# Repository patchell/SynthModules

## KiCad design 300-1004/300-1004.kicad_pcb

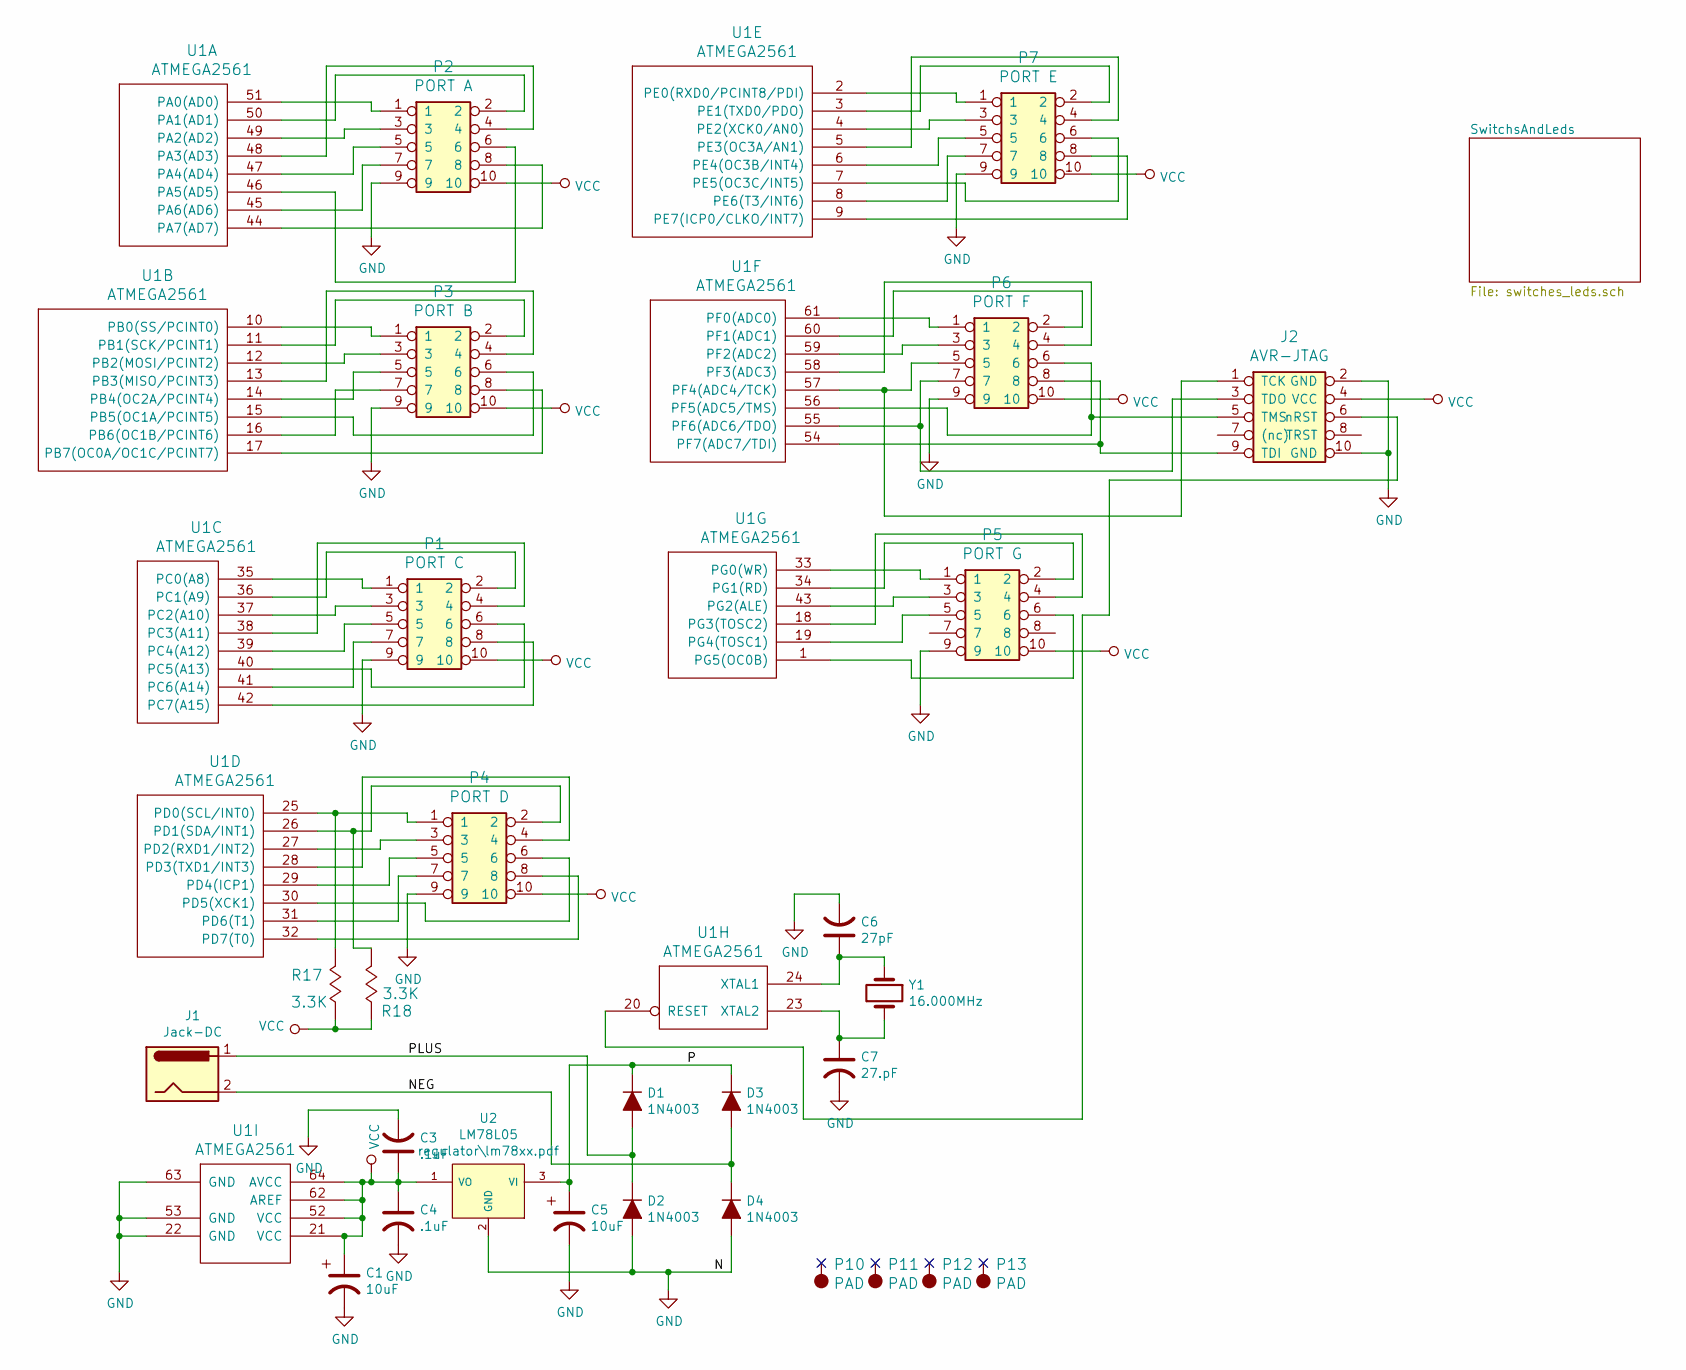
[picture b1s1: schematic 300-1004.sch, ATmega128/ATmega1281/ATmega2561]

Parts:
C1: 10uF; Cap-Pol-Rad-0.2_0.1
C3, C4: .1uF; C_0603_HandSoldering
C5: 10uF; CapPol-Rad-0.2x0.1
C6: 27pF; C_0603_HandSoldering
C7: 27.pF; C_0603_HandSoldering
D1, D2, D3, D4: 1N4003; DIODE0.4
J1: Jack-DC; DC-JACK-CUI-PJ-085AH
J2: AVR-JTAG; IDC5x2_Vert
P1: PORT C; IDC5x2_Vert
P2: PORT A; IDC5x2_Vert
P3: PORT B; IDC5x2_Vert
P4: PORT D; IDC5x2_Vert
P5: PORT G; IDC5x2_Vert
P6: PORT F; IDC5x2_Vert
P7: PORT E; IDC5x2_Vert
P10, P11, P12, P13: PAD
R17, R18: 3.3K; AXIAL0_4
U1: ATMEGA2561; TQFP-64_14x14mm_Pitch0.8mm
U2: LM78L05; TO92
Y1: 16.000MHz; XTAL

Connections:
/NEG: D3.2 (A), D4.1 (K), J1.2
/P: C5.1, D1.1 (K), D3.1 (K), U2.3 (VI)
/PLUS: D1.2 (A), D2.1 (K), J1.1
GND: C1.2, C3.2, C4.2, C5.2, C6.2, C7.2, D2.2 (A), D4.2 (A), J2.2 (GND), J2.10 (GND), P1.9, P2.9, P3.9, P4.9, P5.9, P6.9, P7.9, U1.22 (GND), U1.53 (GND), U1.63 (GND), U2.2 (GND); also elsewhere on the board
unnamed: C6.1, U1.24 (XTAL1), Y1.1
unnamed: C7.1, U1.23 (XTAL2), Y1.2
unnamed: J2.1 (TCK), P6.5, U1.57 (PF4(ADC4/TCK))
unnamed: J2.3 (TDO), P6.7, U1.55 (PF6(ADC6/TDO))
unnamed: J2.5 (TMS), P6.6, U1.56 (PF5(ADC5/TMS))
unnamed: J2.6 (nRST), U1.20 (RESET)
unnamed: J2.9 (TDI), P6.8, U1.54 (PF7(ADC7/TDI))
unnamed: P1.1, U1.35 (PC0(A8))
unnamed: P1.2, U1.36 (PC1(A9))
unnamed: P1.3, U1.37 (PC2(A10))
unnamed: P1.4, U1.38 (PC3(A11))
unnamed: P1.5, U1.39 (PC4(A12))
unnamed: P1.6, U1.40 (PC5(A13))
unnamed: P1.7, U1.41 (PC6(A14))
unnamed: P1.8, U1.42 (PC7(A15))
unnamed: P2.1, U1.51 (PA0(AD0))
unnamed: P2.2, U1.50 (PA1(AD1))
unnamed: P2.3, U1.49 (PA2(AD2))
unnamed: P2.4, U1.48 (PA3(AD3))
unnamed: P2.5, U1.47 (PA4(AD4))
unnamed: P2.6, U1.46 (PA5(AD5))
unnamed: P2.7, U1.45 (PA6(AD6))
unnamed: P2.8, U1.44 (PA7(AD7))
unnamed: P3.1, U1.10 (PB0(SS/PCINT0))
unnamed: P3.2, U1.11 (PB1(SCK/PCINT1))
unnamed: P3.3, U1.12 (PB2(MOSI/PCINT2))
unnamed: P3.4, U1.13 (PB3(MISO/PCINT3))
unnamed: P3.5, U1.14 (PB4(OC2A/PCINT4))
unnamed: P3.6, U1.15 (PB5(OC1A/PCINT5))
unnamed: P3.7, U1.16 (PB6(OC1B/PCINT6))
unnamed: P3.8, U1.17 (PB7(OC0A/OC1C/PCINT7))
unnamed: P4.1, R17.2 (B), U1.25 (PD0(SCL/INT0))
unnamed: P4.2, R18.2 (B), U1.26 (PD1(SDA/INT1))
unnamed: P4.3, U1.27 (PD2(RXD1/INT2))
unnamed: P4.4, U1.28 (PD3(TXD1/INT3))
unnamed: P4.5, U1.29 (PD4(ICP1))
unnamed: P4.6, U1.30 (PD5(XCK1))
unnamed: P4.7, U1.31 (PD6(T1))
unnamed: P4.8, U1.32 (PD7(T0))
unnamed: P5.1, U1.33 (PG0(WR))
unnamed: P5.2, U1.34 (PG1(RD))
unnamed: P5.3, U1.43 (PG2(ALE))
unnamed: P5.4, U1.18 (PG3(TOSC2))
unnamed: P5.5, U1.19 (PG4(TOSC1))
unnamed: P5.6, U1.1 (PG5(OC0B))
unnamed: P6.1, U1.61 (PF0(ADC0))
unnamed: P6.2, U1.60 (PF1(ADC1))
unnamed: P6.3, U1.59 (PF2(ADC2))
unnamed: P6.4, U1.58 (PF3(ADC3))
unnamed: P7.1, U1.2 (PE0(RXD0/PCINT8/PDI))
unnamed: P7.2, U1.3 (PE1(TXD0/PDO))
unnamed: P7.3, U1.4 (PE2(XCK0/AN0))
unnamed: P7.4, U1.5 (PE3(OC3A/AN1))
unnamed: P7.5, U1.6 (PE4(OC3B/INT4))
unnamed: P7.6, U1.7 (PE5(OC3C/INT5))
unnamed: P7.7, U1.8 (PE6(T3/INT6))
unnamed: P7.8, U1.9 (PE7(ICP0/CLKO/INT7))
VCC: C1.1, C3.1, C4.1, J2.4 (VCC), P1.10, P2.10, P3.10, P4.10, P5.10, P6.10, P7.10, R17.1 (A), R18.1 (A), U1.21 (VCC), U1.52 (VCC), U1.62 (AREF), U1.64 (AVCC), U2.1 (VO); also elsewhere on the board

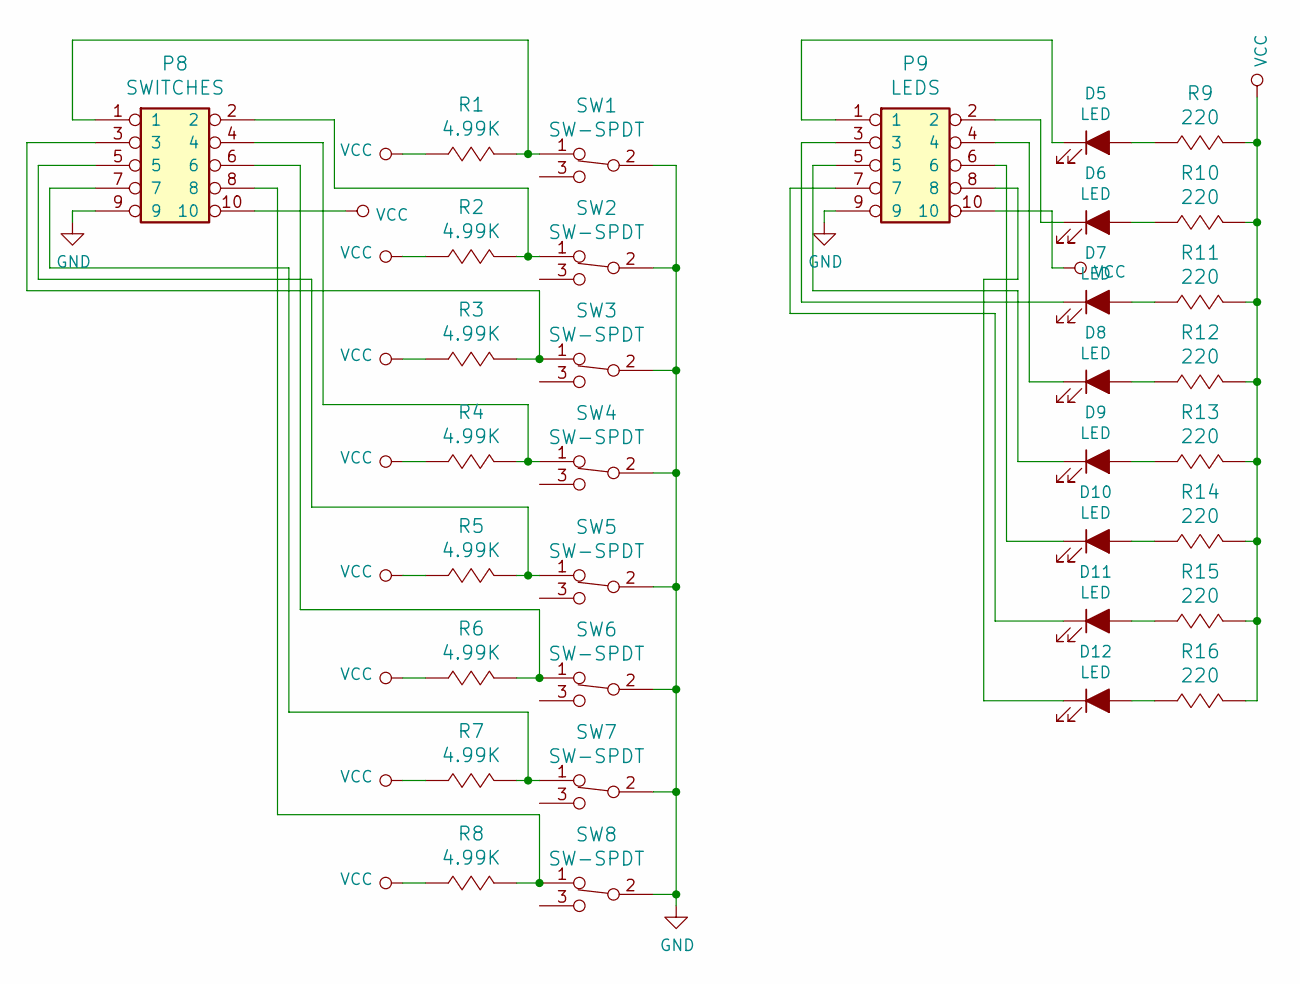
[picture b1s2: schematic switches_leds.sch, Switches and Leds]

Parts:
D5, D6, D7, D8, D9, D10, D11, D12: LED; LED_5.0mm
P8: SWITCHES; IDC5x2_Vert
P9: LEDS; IDC5x2_Vert
R1, R2, R3, R4, R5, R6, R7, R8: 4.99K; AXIAL0_4
R9, R10, R11, R12, R13, R14, R15, R16: 220; AXIAL0_4
SW1, SW2, SW3, SW4, SW5, SW6, SW7, SW8: SW-SPDT; SWITCH_SPDT-OS102011MS2QN1; Part# 611-OS102011MS2QN1

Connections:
GND: P8.9, P9.9, SW1.2, SW2.2, SW3.2, SW4.2, SW5.2, SW6.2, SW7.2, SW8.2; also elsewhere on the board
unnamed: D5.1 (K), P9.1
unnamed: D5.2 (A), R9.1 (A)
unnamed: D6.1 (K), P9.2
unnamed: D6.2 (A), R10.1 (A)
unnamed: D7.1 (K), P9.3
unnamed: D7.2 (A), R11.1 (A)
unnamed: D8.1 (K), P9.4
unnamed: D8.2 (A), R12.1 (A)
unnamed: D9.1 (K), P9.5
unnamed: D9.2 (A), R13.1 (A)
unnamed: D10.1 (K), P9.6
unnamed: D10.2 (A), R14.1 (A)
unnamed: D11.1 (K), P9.7
unnamed: D11.2 (A), R15.1 (A)
unnamed: D12.1 (K), P9.8
unnamed: D12.2 (A), R16.1 (A)
unnamed: P8.1, R1.2 (B), SW1.1
unnamed: P8.2, R2.2 (B), SW2.1
unnamed: P8.3, R3.2 (B), SW3.1
unnamed: P8.4, R4.2 (B), SW4.1
unnamed: P8.5, R5.2 (B), SW5.1
unnamed: P8.6, R6.2 (B), SW6.1
unnamed: P8.7, R7.2 (B), SW7.1
unnamed: P8.8, R8.2 (B), SW8.1
VCC: P8.10, P9.10, R1.1 (A), R2.1 (A), R3.1 (A), R4.1 (A), R5.1 (A), R6.1 (A), R7.1 (A), R8.1 (A), R9.2 (B), R10.2 (B), R11.2 (B), R12.2 (B), R13.2 (B), R14.2 (B), R15.2 (B), R16.2 (B); also elsewhere on the board

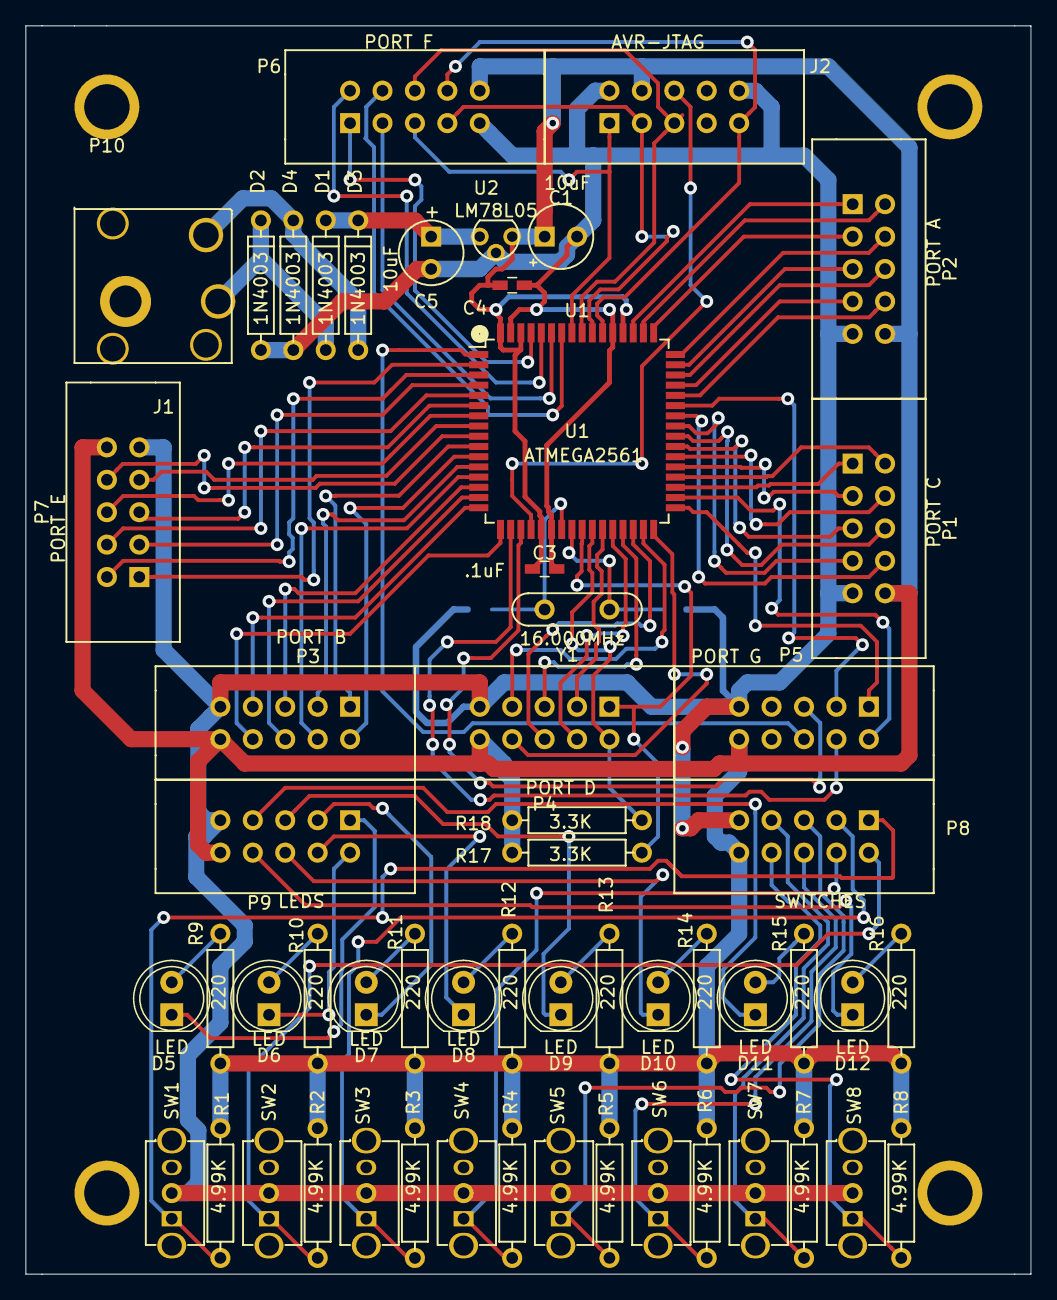
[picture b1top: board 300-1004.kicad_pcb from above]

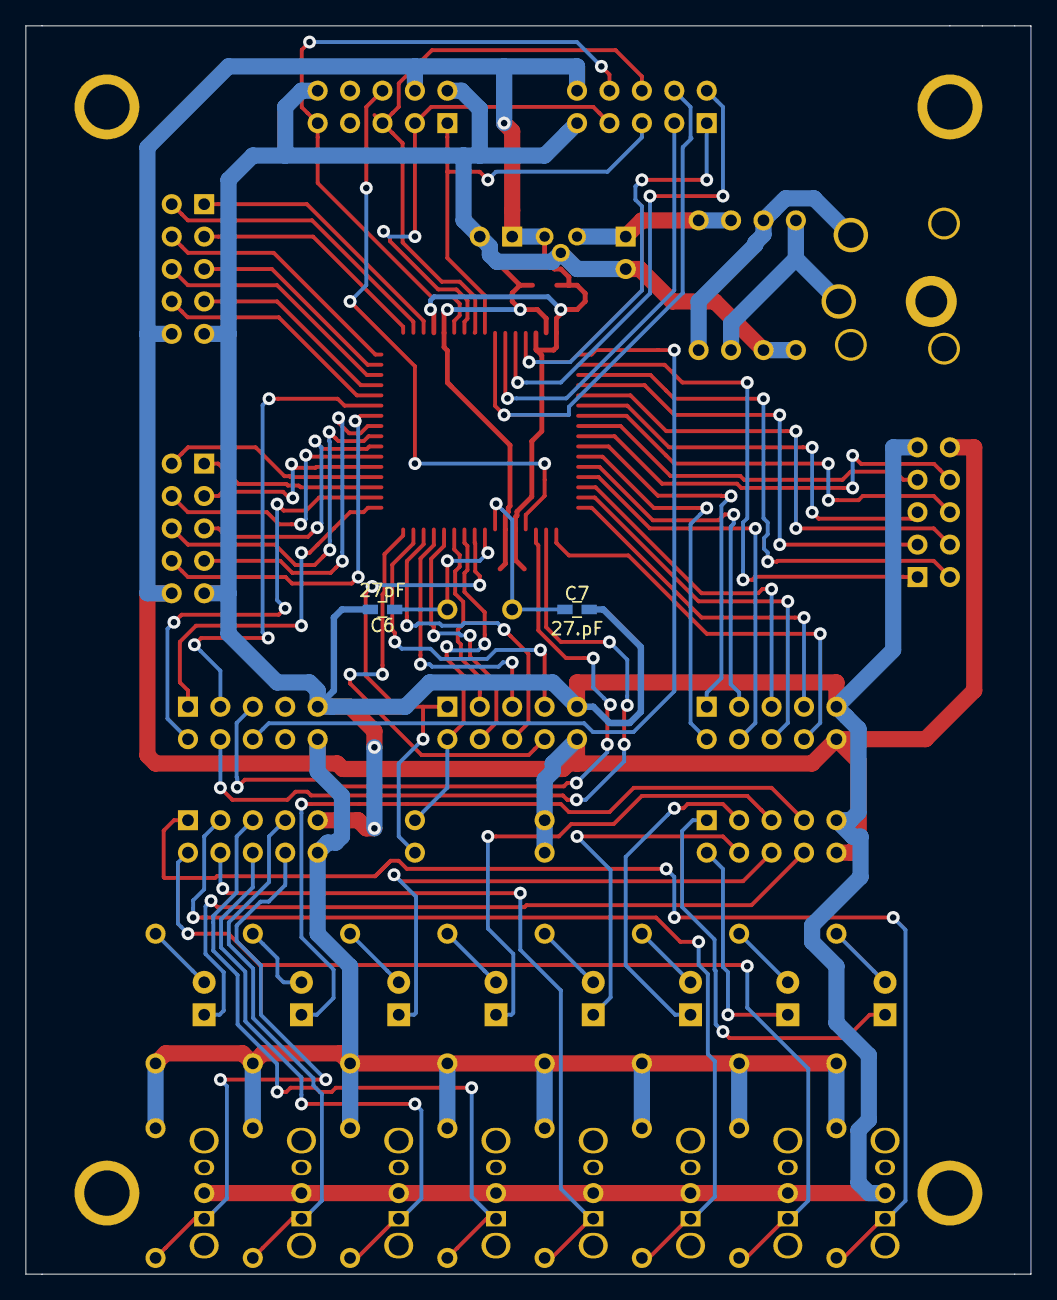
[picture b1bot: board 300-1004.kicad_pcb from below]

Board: 2 copper layers, 78.7 x 97.8 mm, 62 parts (2 on the bottom side), 86 nets.

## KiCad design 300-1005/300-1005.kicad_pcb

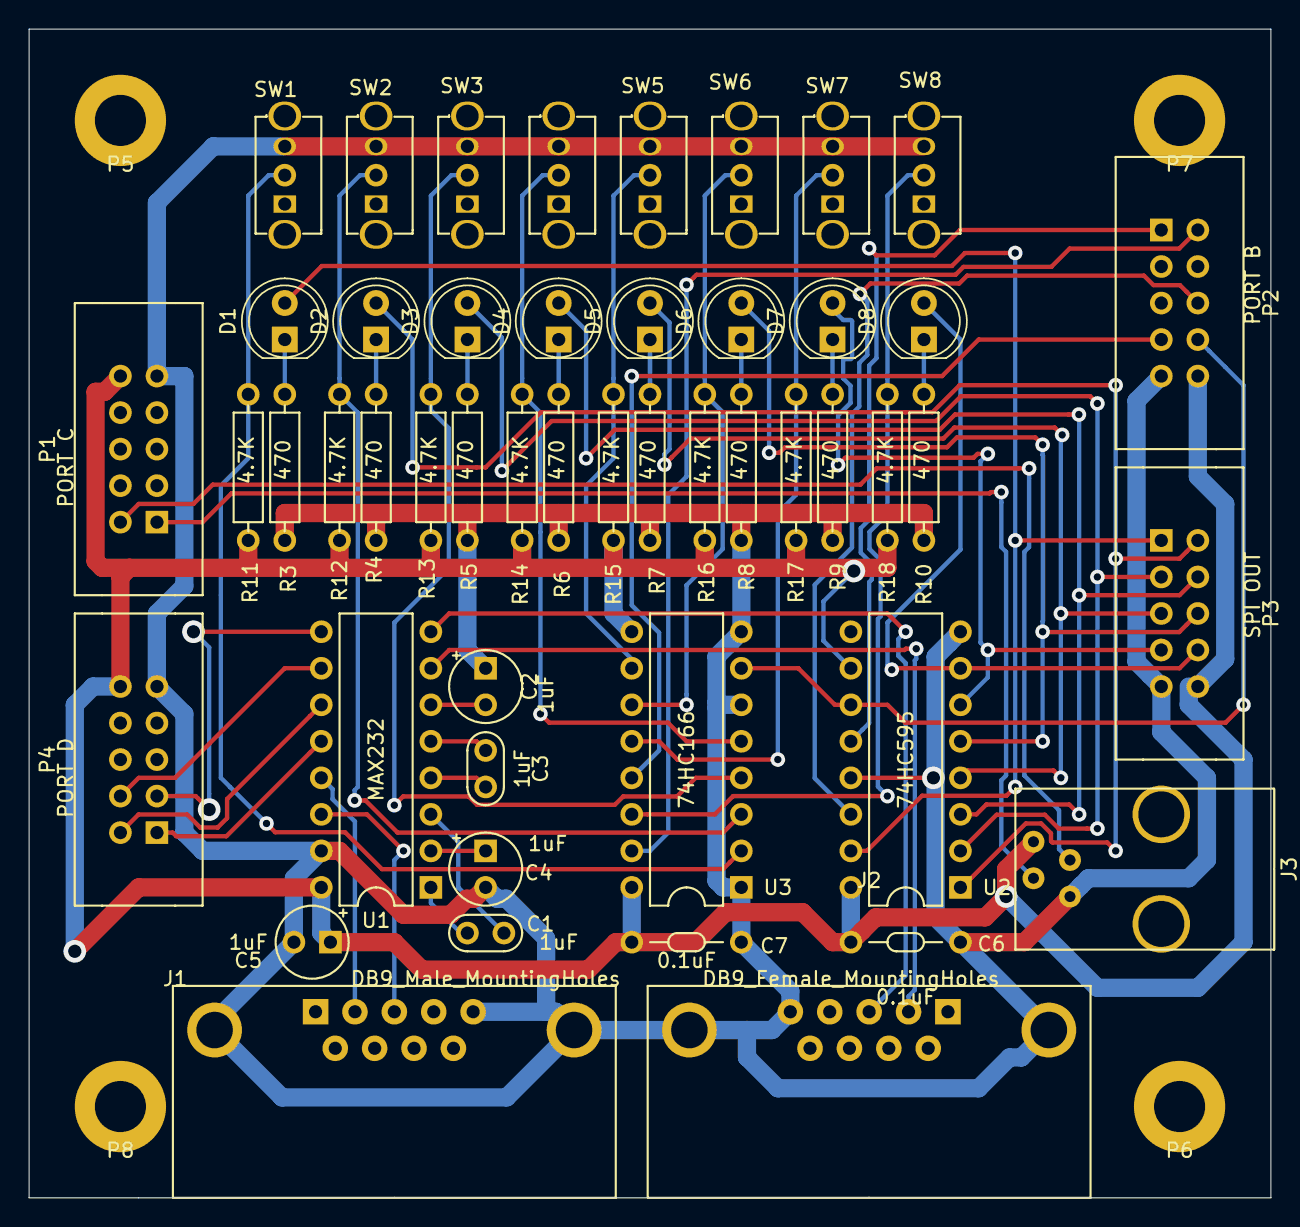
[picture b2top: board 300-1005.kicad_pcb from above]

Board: 2 copper layers, 86.4 x 81.3 mm, 53 parts (0 on the bottom side), 47 nets.

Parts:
C1, C3: 1uF; CAP-0.1
C2, C4, C5: 1uF; Cap-Pol-Rad-0.2_0.1
C6, C7: 0.1uF; CAP-Bypass-0_3
D1, D2, D3, D4, D5, D6, D7, D8: LED; LED_5.0mm
J1: DB9_Male_MountingHoles; DSUB-9P
J2: DB9_Female_MountingHoles; DSUB-9S
J3: RJ9; RJ9-PCB-Conn
P1: PORT C; IDC5x2_Vert
P2: PORT B; IDC5x2_Vert
P3: SPI OUT; IDC5x2_Vert
P4: PORT D; IDC5x2_Vert
P5, P6, P7, P8: PAD
R3, R4, R5, R6, R7, R8, R9, R10: 470; AXIAL0_4
R11, R12, R13, R14, R15, R16, R17, R18: 4.7K; AXIAL0_4
SW1, SW2, SW3, SW4, SW5, SW6, SW7, SW8: SW-SPDT; SWITCH_SPDT-OS102011MS2QN1
U1: MAX232; DIP-16
U2: 74HC595; DIP-16
U3: 74HC166; DIP-16

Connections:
+5V0: C5.1, C6.1, C7.1, J3.4, P1.10, P2.10, P3.10, P4.10, R11.2, R12.2, R13.2, R14.2, R15.2, R16.2, R17.2, R18.2, U1.16, U2.10, U2.16, U3.9, U3.16
/LATCH_SERIN: P2.2, U3.15
/LATCH_SEROUT: P2.1, U2.12
/MISO: P2.7, U3.13
/MOSI: P2.6, U2.14
/RXD0: P4.1, U1.12
/RXD1: P4.3, U1.9
/S1: R11.1, SW1.2, U3.2
/S2: R12.1, SW2.2, U3.3
/S3: R13.1, SW3.2, U3.4
/S4: R14.1, SW4.2, U3.5
/S5: R15.1, SW5.2, U3.10
/S6: R16.1, SW6.2, U3.11
/S7: R17.1, SW7.2, U3.12
/S8: R18.1, SW8.2, U3.14
/SCK: P2.8, U2.11, U3.7
/SCL: J3.2, P1.1
/SDA: J3.3, P1.2
/SPI0: D1.2, P3.1, U2.15
/SPI1: D2.2, P3.2, U2.1
/SPI2: D3.2, P3.3, U2.2
/SPI3: D4.2, P3.4, U2.3
/SPI4: D5.2, P3.5, U2.4
/SPI5: D6.2, P3.6, U2.5
/SPI6: D7.2, P3.7, U2.6
/SPI7: D8.2, P3.8, U2.7
/TXD0: P4.2, U1.11
/TXD1: P4.4, U1.10
GND: C2.1, C4.2, C5.2, C6.2, C7.2, J1.0, J1.5, J2.0, J2.5, J3.1, P1.9, P2.9, P3.9, P4.9, R3.2, R4.2, R5.2, R6.2, R7.2, R8.2, R9.2, R10.2, SW1.3, SW2.3, SW3.3, SW4.3, SW5.3, SW6.3, SW7.3, SW8.3, U1.15, U2.8, U2.13, U3.1, U3.6, U3.8
unnamed: C1.1, U1.1
unnamed: C1.2, U1.3
unnamed: C2.2, U1.6
unnamed: C3.1, U1.4
unnamed: C3.2, U1.5
unnamed: C4.1, U1.2
unnamed: D1.1, R3.1
unnamed: D2.1, R4.1
unnamed: D3.1, R5.1
unnamed: D4.1, R6.1
unnamed: D5.1, R7.1
unnamed: D6.1, R8.1
unnamed: D7.1, R9.1
unnamed: D8.1, R10.1
unnamed: J1.2, U1.13
unnamed: J1.3, U1.14
unnamed: J2.2, U1.7
unnamed: J2.3, U1.8

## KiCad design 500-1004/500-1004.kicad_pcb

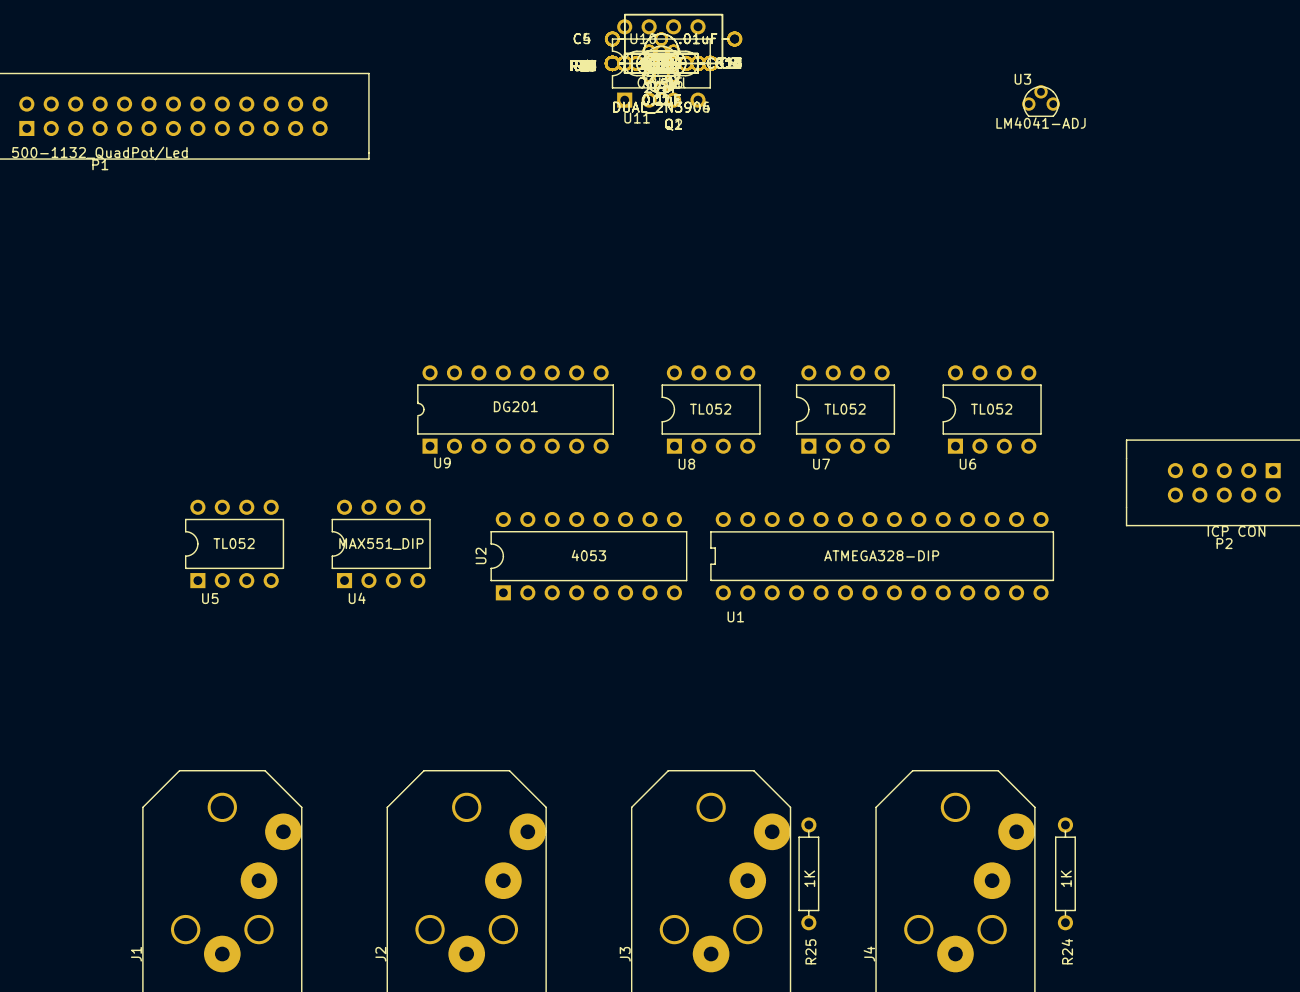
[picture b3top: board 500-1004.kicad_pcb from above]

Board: 2 copper layers, 67 parts (0 on the bottom side), 59 nets, no tracks yet.

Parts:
C1, C2: 27pF; CAP-0.1
C3, C6: Cap; CAP-GREENIE-0.2
C4, C5: .01uF; CAP-AXIAL-0.5x0.2
C7, C8, C9, C10, C11, C12, C13, C14, C15, C16, C17: 0.1uF; CAP-Bypass-0.3
D1, D2, D3, D4, D5: D_ALT; DIODE0.4
J1: GATE; PHONE-SC112A
J2, J3, J4: OUT; PHONE-SC112A
P1: 500-1132_QuadPot/Led; IDC-13x2
P2: ICP CON; IDC5x2_Vert
Q1: DUAL_2N3904; DUAL_TO92
Q2: DUAL_2N3906; DUAL_TO92
R1, R6, R7, R8, R9, R10, R11, R12, R13, R14, R15, R19, R20: 100K; AXIAL0.4
R2, R3, R4, R5: 470; AXIAL0.4
R16, R18, R22: 10K; AXIAL0.4
R17, R21: 182; AXIAL0.4
R23, R24, R25: 1K; AXIAL0.4
U1: ATMEGA328-DIP; DIP28.3
U2: 4053; DIP-16.3
U3: LM4041-ADJ; TO92
U4: MAX551_DIP; DIP8.3
U5, U6, U7, U8, U11: TL052; DIP8.3
U9: DG201; DIP16.3
U10: 78L05; TO92
Y1: Crystal; XTAL

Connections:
+15V0: C7.1, C8.1, C10.1, C11.1, C15.1, R13.1, U5.8, U6.8, U8.8, U9.13, U10.3, U11.8
-15V0: C9.1, C12.1, C13.1, C14.1, C16.1, R8.2, R15.2, U5.4, U6.4, U8.4, U9.4, U11.4
/ATTACK: P1.2, U1.23
/DECAY: P1.6, U1.24
/DONE: D5.1, R20.1, U1.4
/GATE: D1.1, D2.2, R1.1, U1.5
/LD_DAC: U1.2, U4.4
/LED0: R2.2, U1.6
/LED1: R3.2, U1.11
/LED2: R4.2, U1.12
/LED3: R5.2, U1.13
/MISO: U1.18, U2.15
/MOSI: U1.17, U2.14
/RELEASE: P1.14, U1.26
/RST: P2.5, U1.1, U2.9, U2.10, U2.11
/SCK: U1.19, U2.4
/SH0: U1.14, U9.1
/SH1: U1.15, U9.8
/SUSTAIN: P1.10, U1.25
GND: C1.2, C2.2, C4.2, C5.2, C7.2, C8.2, C9.2, C10.2, C11.2, C12.2, C13.2, C14.2, C15.2, C16.2, C17.2, D1.2, D5.2, J1.1, J2.1, J3.1, J4.1, P1.3, P1.7, P1.11, P1.15, P2.4, P2.6, P2.8, P2.10, R6.1, R11.2, R17.2, R21.2, U1.8, U1.22, U2.6, U2.7, U3.2, U4.2, U6.3, U7.3, U8.5, U9.5, U10.2
unnamed: C1.1, U1.10, Y1.1
unnamed: C2.1, U1.9, Y1.2
unnamed: C3.1, Q1.3, Q2.3, R16.2, U8.6
unnamed: C3.2, R18.2, U8.7
unnamed: C4.1, U8.3, U9.3
unnamed: C5.1, U9.6, U11.5
unnamed: C6.1, Q1.6, Q2.6, U6.2
unnamed: C6.2, R9.1, R23.2, R24.2, R25.2, U6.1
unnamed: D3.1, U5.1
unnamed: D3.2, D4.2, R19.2, R20.2
unnamed: D4.1, U6.7
unnamed: J1.3, R1.2
unnamed: J2.3, R23.1
unnamed: J3.3, R25.1
unnamed: J4.3, R24.1
unnamed: P1.18, R2.1
unnamed: P1.20, R3.1
unnamed: P1.22, R4.1
unnamed: P1.24, R5.1
unnamed: P2.1, U2.12
unnamed: P2.7, U2.5
unnamed: P2.9, U2.2
unnamed: Q1.1, Q1.4, Q2.1, Q2.4, R18.1
unnamed: Q1.2, Q2.5, R21.1, R22.1
unnamed: Q1.5, Q2.2, R17.1
unnamed: R6.2, R7.1, U3.3
unnamed: R7.2, R8.1, U3.1, U4.7
unnamed: R10.1, U8.1, U8.2
unnamed: R10.2, R11.1, U5.5
unnamed: R9.2, R12.1, U5.6
unnamed: R12.2, R16.1, U5.2, U5.7, U6.5
unnamed: R13.2, R14.1, U5.3
unnamed: R14.2, R15.1, U6.6
unnamed: R22.2, U11.6, U11.7
unnamed: U2.3, U4.6
unnamed: U2.13, U4.5
unnamed: U4.1, U7.2
unnamed: U4.8, U7.1, U9.2, U9.7
VCC: C17.1, D2.1, P1.1, P1.5, P1.9, P1.13, P1.17, P1.19, P1.21, P1.23, P2.2, R19.1, U1.7, U1.21, U4.3, U10.1

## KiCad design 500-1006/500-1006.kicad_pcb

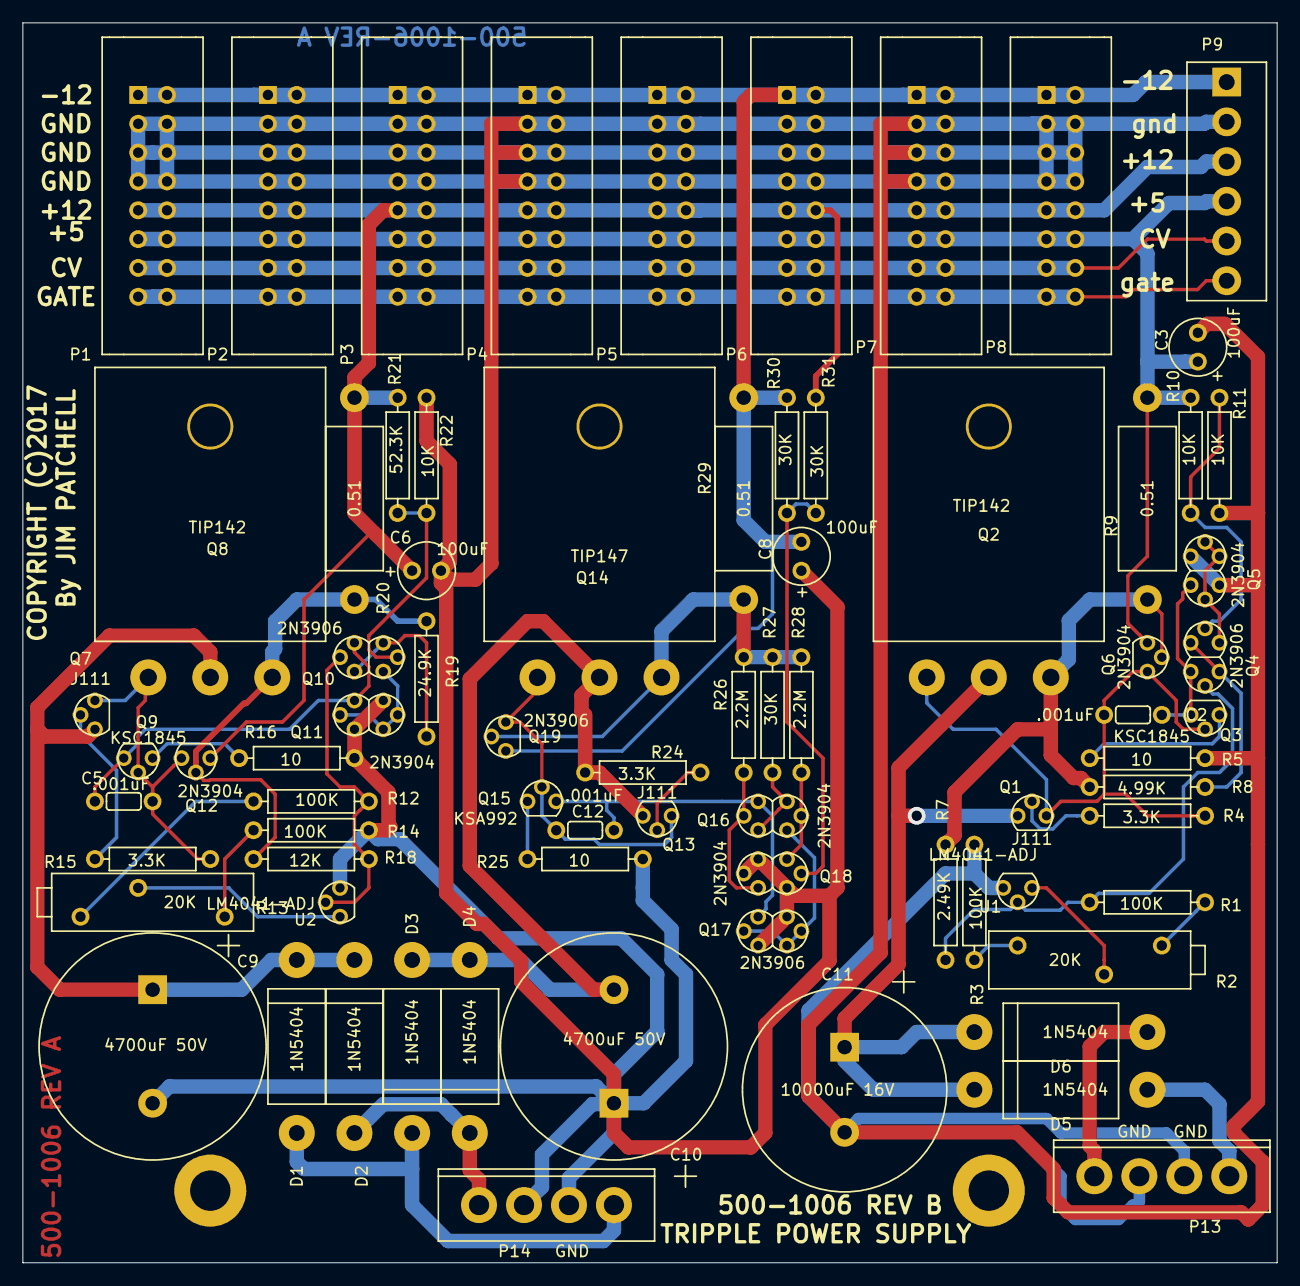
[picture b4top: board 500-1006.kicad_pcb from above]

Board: 2 copper layers, 110.5 x 109.2 mm, 77 parts (0 on the bottom side), 47 nets.

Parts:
C2, C5, C12: .001uF; CAP-GREENIE-0.2
C3, C6, C8: 100uF; CapPol-Rad-0.2x0.1
C9, C10: 4700uF 50V; CP_RAD_20mmx10mm
C11: 10000uF 16V; CP_RAD_18mmx7_5mm
D1, D2, D3, D4, D5, D6: 1N5404; DIODE0.6X0.2
P1, P2, P3, P4, P5, P6, P7, P8: EurorackPower16pin; IDC8x2_Vert
P9: Header_6x1; TERMINAL-BLOCK-SCREWS
P13, P14: Header_4x1; MTA0156x4_Vert
P18, P19: PAD; MountingHole_140
Q1, Q7, Q13: J111; TO92
Q2, Q8: TIP142; TO-264
Q3, Q9: KSC1845; TO92
Q4, Q10, Q17: 2N3906; DUAL_TO92
Q5, Q11, Q16, Q18: 2N3904; DUAL_TO92
Q6, Q12: 2N3904; TO92
Q14: TIP147; TO-264
Q15: KSA992; TO92
Q19: 2N3906; TO92
R1, R3, R12, R14: 100K; AXIAL0.4
R2, R13: 20K; Trimpot-3006
R4, R15, R24: 3.3K; AXIAL0.4
R5, R16, R25: 10; AXIAL0.4
R7: 2.49K; AXIAL0.4
R8: 4.99K; AXIAL0.4
R9, R20, R29: 0.51; AXIAL0.7X0.2
R10, R11, R22: 10K; AXIAL0.4
R18: 12K; AXIAL0.4
R19: 24.9K; AXIAL0.4
R21: 52.3K; AXIAL0.4
R26, R28: 2.2M; AXIAL0.4
R27, R30, R31: 30K; AXIAL0.4
U1, U2: LM4041-ADJ; TO92

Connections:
+5V0: C3.1, P1.11, P1.12, P2.11, P2.12, P3.11, P3.12, P4.11, P4.12, P5.11, P5.12, P6.11, P6.12, P7.11, P7.12, P8.11, P8.12, P9.4, Q6.1, R9.2, R10.1
+12V0: C6.1, P1.9, P1.10, P2.9, P2.10, P3.9, P3.10, P4.9, P4.10, P5.9, P5.10, P6.9, P6.10, P7.9, P7.10, P8.9, P8.10, P9.3, Q12.1, R20.2, R21.1, R31.2
-12V0: C8.2, P1.1, P1.2, P2.1, P2.2, P3.1, P3.2, P4.1, P4.2, P5.1, P5.2, P6.1, P6.2, P7.1, P7.2, P8.1, P8.2, P9.1, Q19.1, R29.1, R30.1
/AC_5A: D5.2, P13.1
/AC_5B: D6.2, P13.4
/AC_15_A: D1.2, D3.1, P14.1
/AC_15_B: D2.2, D4.1, P14.4
/CV: P1.13, P1.14, P2.13, P2.14, P3.13, P3.14, P4.13, P4.14, P5.13, P5.14, P6.13, P6.14, P7.13, P7.14, P8.13, P8.14, P9.5
/GATE: P1.15, P1.16, P2.15, P2.16, P3.15, P3.16, P4.15, P4.16, P5.15, P5.16, P6.15, P6.16, P7.15, P7.16, P8.15, P8.16, P9.6
/Negative Supply A/-15V_CS: Q14.3, Q19.2, R26.1, R27.1, R28.1, R29.2
/PositiveSupplyA/+15V_CS: Q8.3, Q12.2, R18.1, R19.1, R20.1
/Ppositive_5_Volts/5V_CS: Q2.3, Q6.2, R7.1, R8.1, R9.1
/UNREG_5: C11.1, D5.1, D6.1, Q1.1, Q2.2
/UNREG_15: C9.1, D1.1, D2.1, Q7.1, Q8.2
/UNREG_NEG: C10.2, D3.2, D4.2, Q13.3, Q14.2, R24.1
GND: C3.2, C6.2, C8.1, C9.2, C10.1, C11.2, P1.3, P1.4, P1.5, P1.6, P1.7, P1.8, P2.3, P2.4, P2.5, P2.6, P2.7, P2.8, P3.3, P3.4, P3.5, P3.6, P3.7, P3.8, P4.3, P4.4, P4.5, P4.6, P4.7, P4.8, P5.3, P5.4, P5.5, P5.6, P5.7, P5.8, P6.3, P6.4, P6.5, P6.6, P6.7, P6.8, P7.3, P7.4, P7.5, P7.6, P7.7, P7.8, P8.3, P8.4, P8.5, P8.6, P8.7, P8.8, P9.2, P13.2, P13.3, P14.2, P14.3, Q5.1, Q5.4, Q11.1, Q11.4, Q17.1, Q17.4, Q18.2, Q18.3, Q18.6, R3.2, R5.2, R11.2, R14.2, R16.2, R22.2, R25.2, U1.3, U2.3
unnamed: C2.1, Q1.3, Q2.1, Q3.2, Q6.3, R4.2
unnamed: C2.2, Q3.3, Q4.3, Q5.3
unnamed: C5.1, Q7.3, Q8.1, Q9.2, Q12.3, R15.2
unnamed: C5.2, Q9.3, Q10.3, Q11.3
unnamed: C12.1, Q13.1, Q14.1, Q15.2, Q19.3
unnamed: C12.2, Q15.3, Q16.6, Q17.3
unnamed: Q1.2, R4.1
unnamed: Q3.1, R5.1
unnamed: Q4.1, Q4.4, R8.2
unnamed: Q4.2, R1.1, R7.2, U1.2
unnamed: Q4.5, R10.2, R11.1
unnamed: Q4.6, Q5.2, Q5.5, Q5.6
unnamed: Q7.2, R15.1
unnamed: Q9.1, R16.1
unnamed: Q10.1, Q10.4, R19.2
unnamed: Q10.2, R12.1, R18.2, U2.2
unnamed: Q10.5, R21.2, R22.1
unnamed: Q10.6, Q11.2, Q11.5, Q11.6
unnamed: Q13.2, R24.2
unnamed: Q15.1, R25.1
unnamed: Q16.1, Q16.4, R27.2
unnamed: Q16.2, Q18.4, R28.2
unnamed: Q16.3, Q17.2, Q17.5, Q17.6
unnamed: Q16.5, Q18.1, R26.2
unnamed: Q18.5, R30.2, R31.1
unnamed: R1.2, R2.1
unnamed: R2.2, U1.1
unnamed: R2.3, R3.1
unnamed: R12.2, R13.1
unnamed: R13.2, U2.1
unnamed: R13.3, R14.1

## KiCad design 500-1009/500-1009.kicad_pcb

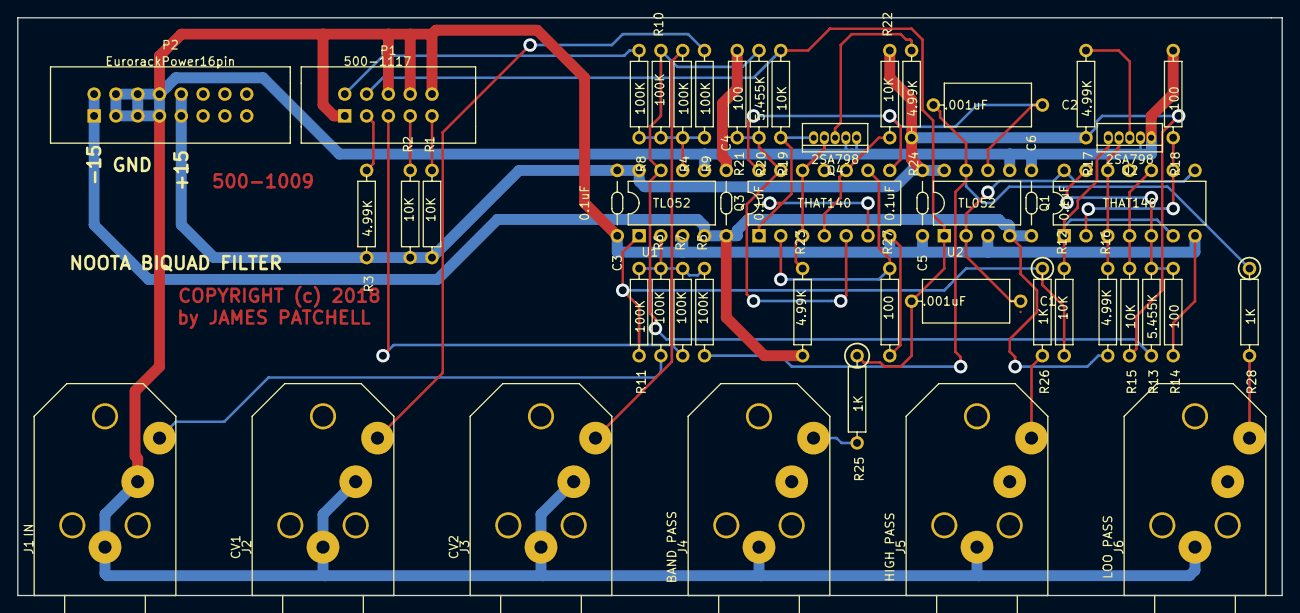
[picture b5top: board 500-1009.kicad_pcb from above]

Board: 2 copper layers, 147.3 x 67.3 mm, 48 parts (0 on the bottom side), 34 nets.

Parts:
C1, C2: .001uF; CAP-AXIAL-0.5x0.2
C3, C4, C5, C6: 0.1uF; CAP-Bypass-0.3
J1: IN; PHONE-SC112A
J2: CV1; PHONE-SC112A
J3: CV2; PHONE-SC112A
J4: BAND PASS; PHONE-SC112A
J5: HIGH PASS; PHONE-SC112A
J6: LOO PASS; PHONE-SC112A
P1: 500-1117; IDC5x2_Vert
P2: EurorackPower16pin; IDC8x2_Vert
Q1, Q3: THAT140; DIP-14.3
Q2, Q4: 2SA798
R1, R2, R12, R15, R19, R22: 10K; AXIAL0.4
R3, R16, R17, R23, R24: 4.99K; AXIAL0.4
R4, R5, R6, R7, R8, R9, R10, R11: 100K; AXIAL0.4
R13, R20: 5.455K; AXIAL0.4
R14, R18, R21, R27: 100; AXIAL0.4
R25, R26, R28: 1K; AXIAL0.4
U1, U2: TL052; DIP8.3

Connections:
+15V0: C3.1, C5.1, P2.9, P2.10, R1.2, R2.2, R3.1, R15.1, R17.1, R22.1, R24.1, U1.8, U2.8
-15V0: C4.1, C6.1, P2.1, P2.2, R16.2, R23.2, U1.4, U2.4
GND: C3.2, C4.2, C5.2, C6.2, J1.1, J1.2, J2.1, J2.2, J3.1, J3.2, J4.1, J5.1, J6.1, P1.1, P1.6, P1.8, P1.10, P2.3, P2.4, P2.5, P2.6, P2.7, P2.8, Q1.7, Q2.4, Q2.5, Q3.7, Q4.4, Q4.5, R14.1, R18.2, R21.2, R27.2, U1.3, U1.5, U2.3, U2.5
unnamed: C1.1, Q1.8, Q1.14, U2.2
unnamed: C1.2, P1.4, R19.2, R25.2, U2.1
unnamed: C2.1, Q3.8, Q3.14, U2.6
unnamed: C2.2, R5.2, R28.2, U2.7
unnamed: J1.3, R6.2
unnamed: J2.3, R9.2
unnamed: J3.3, R4.2
unnamed: J4.3, R25.1
unnamed: J5.3, R26.1
unnamed: J6.3, R28.1
unnamed: P1.2, R8.2
unnamed: P1.3, R3.2
unnamed: P1.5, R7.2
unnamed: P1.7, R2.1
unnamed: P1.9, R1.1
unnamed: Q1.1, Q1.6, Q2.1, R12.1
unnamed: Q1.2, Q1.9, R18.1
unnamed: Q1.4, Q1.10, R15.2
unnamed: Q1.3, Q1.12, Q2.2, R16.1
unnamed: Q1.5, Q1.13, R13.2, R14.2
unnamed: Q2.3, R17.2
unnamed: Q3.1, Q3.6, Q4.1, R19.1
unnamed: Q3.2, Q3.9, R27.1
unnamed: Q3.4, Q3.10, R22.2
unnamed: Q3.3, Q3.12, Q4.2, R23.1
unnamed: Q3.5, Q3.13, R20.1, R21.1
unnamed: Q4.3, R24.2
unnamed: R10.1, R13.1, R20.2, U1.7
unnamed: R4.1, R8.1, R9.1, R10.2, U1.6
unnamed: R11.1, R12.2, R26.2, U1.1
unnamed: R5.1, R6.1, R7.1, R11.2, U1.2

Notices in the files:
500-1006/500-1006.kicad_pcb:
COPYRIGHT (C)2017
500-1009/500-1009.kicad_pcb:
COPYRIGHT (c) 2018
